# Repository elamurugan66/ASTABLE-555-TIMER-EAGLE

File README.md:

# ASTABLE-555-TIMER-EAGLE
555 TIMER USING AUTODESK

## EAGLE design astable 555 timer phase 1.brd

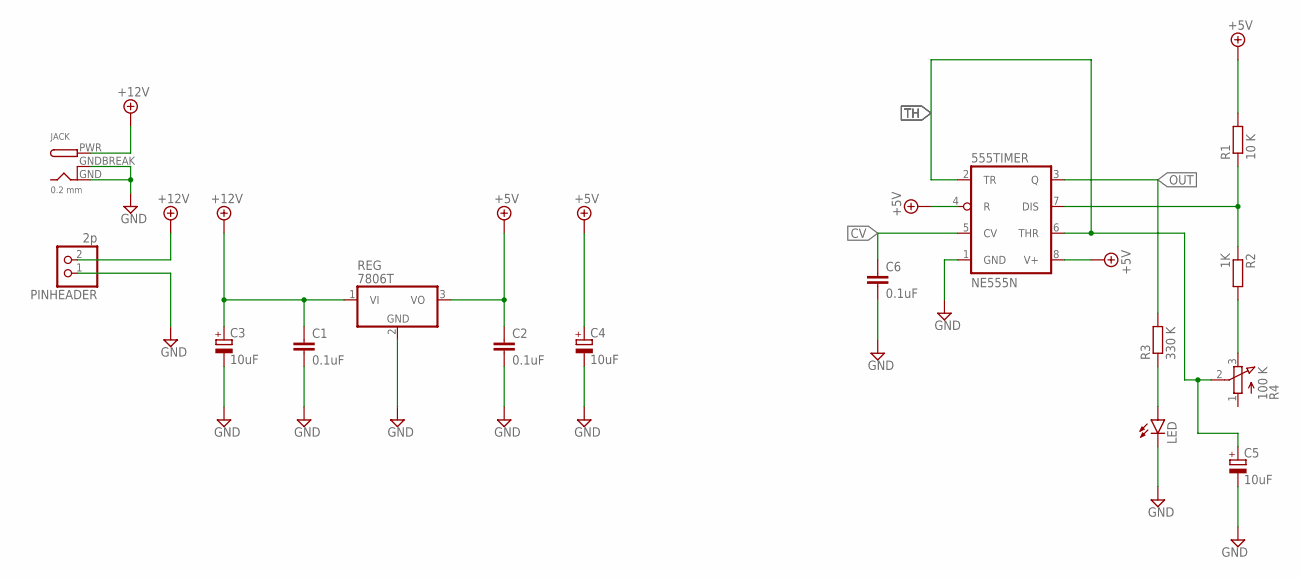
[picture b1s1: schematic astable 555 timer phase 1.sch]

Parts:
555TIMER: NE555N; DIL08
C1, C2, C6: 0.1uF; C050-030X075
C3, C4, C5: 10uF; E3,5-8
JACK: 0.2 mm; DCJACK_2MM_PTH
LED: LED5MM
PINHEADER: 2p; 1X02
R1: 10 K; 0207/10
R2: 1K; 0207/10
R3: 330 K; 0207/10
R4: 100 K; 3RP/1610N
REG: 7806T; TO220H

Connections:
+5V: 555TIMER.4 (R), 555TIMER.8 (V+), C2.1, C4.+, R1.2, REG.3 (VO)
+12V: C1.1, C3.+, JACK.PWR, PINHEADER.2, REG.1 (VI)
CV: 555TIMER.5 (CV), C6.1
GND: 555TIMER.1 (GND), C1.2, C2.2, C3.-, C4.-, C5.-, C6.2, JACK.GND, JACK.GNDBREAK, LED.K (C), PINHEADER.1, REG.2 (GND)
unnamed: 555TIMER.7 (DIS), R1.1, R2.1
unnamed: R2.2, R4.3 (E)
unnamed: LED.A, R3.1
OUT: 555TIMER.3 (Q), R3.2
TH: 555TIMER.2 (TR), 555TIMER.6 (THR), C5.+, R4.2 (S)

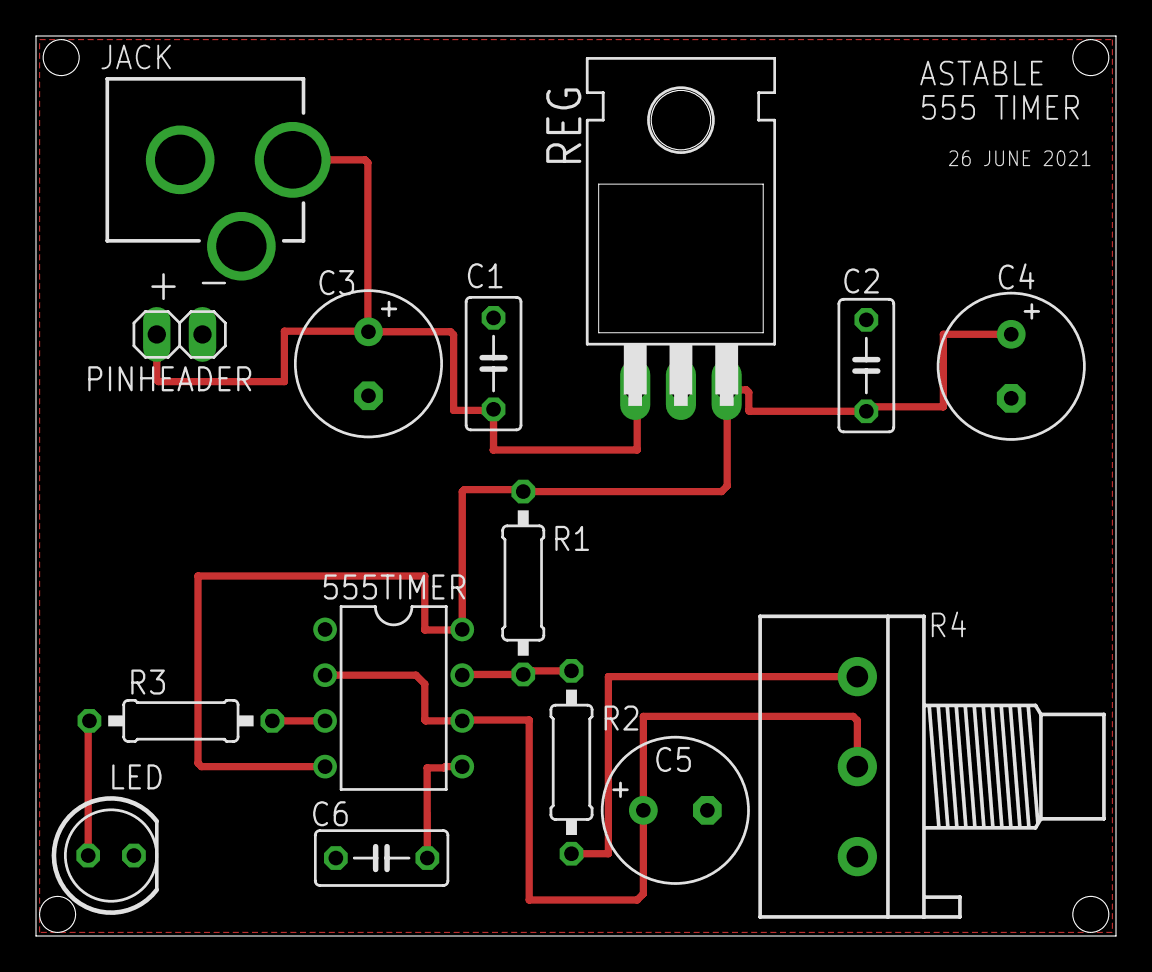
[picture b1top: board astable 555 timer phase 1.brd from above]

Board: 2 copper layers, 60.0 x 50.0 mm, 15 parts (0 on the bottom side), 9 nets.
